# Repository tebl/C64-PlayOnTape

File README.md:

# C64 PlayOnTape
Remember waiting around for what sometimes would feel like forever, just to get your favourite game loaded from your trusty datasette? Well, now you can now attempt to return to a slightly less irritating version of those good old days - loading games'll take just as long as they did back then, just without the need to fiddle with the azimuth setting. Based on the rather excellent [tapuino](https://github.com/sweetlilmre/tapuino) project, there's even an accompanying [blog](http://sweetlilmre.blogspot.com/search/label/Tapuino) that included instructions on how to build one all by yourself.

Personally I haven't had much success building prototypes on breadboards, veroboard and almost every other option available within my severely limited cashflow. I highly suspect that part of this is due to my tendency for only buying the cheapest stuff around, so in order to keep myself sane I went straight from the blog onto designing the PCBs in KiCAD. On the plus side the files are here for anyone to enjoy, just remember that there's no warranty beyond my promise that it worked that one time I built one. If your C64 blows up due to problems assembling or using it, know that I'll be happy to take it off your hands for spare parts.

- [C64 PlayOnTape](#c64-playontape)
  - [1.1> Modules](#11-modules)
  - [1.2> Acknowledgements](#12-acknowledgements)

## 1.1> Modules
For the technical details as well as information regarding the modules included by this specific github project, consult the table below. Follow the documentation links for build instructions, BOM and anything else you'd for that specific module. Faceplates and any backplates listed are for the most most part only decorative, allowing you to put together something similar to a case without actually requiring a 3d-printer. Also, check out the [schematics](https://github.com/tebl/C64-PlayOnTape/tree/main/documentation/schematic) for more information about the electronic side of things.

| Module                 | Required    | Documentation                      | Order      |
| ---------------------- | ----------- | ---------------------------------- | ---------- |
| [C64 PlayOnTape Module](https://github.com/tebl/C64-PlayOnTape/tree/main/PlayOnTape%20Module) | Yes | [Documentation](https://github.com/tebl/C64-PlayOnTape/blob/main/PlayOnTape%20Module/README.md), [BOM](https://github.com/tebl/C64-PlayOnTape/blob/main/PlayOnTape%20Module/README.md#3-bom), [Getting started](https://github.com/tebl/C64-PlayOnTape/blob/main/documentation/getting_started.md) | [PCBWay](https://www.pcbway.com/project/shareproject/C64_PlayOnTape_7281e4c0.html)
| [C64 PlayOnTape Adapter](https://github.com/tebl/C64-PlayOnTape/tree/main/PlayOnTape%20Adapter) | Yes | [Documentation](https://github.com/tebl/C64-PlayOnTape/blob/main/PlayOnTape%20Adapter/README.md), [BOM](https://github.com/tebl/C64-PlayOnTape/blob/main/PlayOnTape%20Adapter/README.md#3-bom) | [PCBWay](https://www.pcbway.com/project/shareproject/C64_PlayOnTape_Adapter_6b7e3197.html)
| [PlayOnTape Backplate](https://github.com/tebl/C64-PlayOnTape/tree/main/faceplates/PlayOnTape%20Backplate) | No | [Documentation](https://github.com/tebl/C64-PlayOnTape/blob/main/faceplates/PlayOnTape%20Backplate/README.md) | [PCBWay](https://www.pcbway.com/project/shareproject/C64_PlayOnTape_Backplate_04d028fa.html)
| [PlayOnTape Faceplate (A1)](https://github.com/tebl/C64-PlayOnTape/tree/main/faceplates/PlayOnTape%20Faceplate%20A1) | Recommended | [Documentation](https://github.com/tebl/C64-PlayOnTape/blob/main/faceplates/PlayOnTape%20Faceplate%20A1/README.md), [BOM](https://github.com/tebl/C64-PlayOnTape/blob/main/faceplates/PlayOnTape%20Faceplate%20A1/README.md#3-bom) | [PCBWay](https://www.pcbway.com/project/shareproject/C64_PlayOnTape_Faceplate_FA1_dac67ded.html)

## 1.2> Acknowledgements
Everything comes from something, in particular when it comes to most of my electronics projects. I mainly build things I would like to own, often doing a respin to fit my own particular style and preferences with most of the hardest parts of the designs already provided by people more knowledgable than I. As already mentioned, my designs are based on the rather excellent [tapuino](https://github.com/sweetlilmre/tapuino) project with a new name just to keep things separate, for more details on how it functions - check out his accompanying [blog](http://sweetlilmre.blogspot.com/search/label/Tapuino) as well.

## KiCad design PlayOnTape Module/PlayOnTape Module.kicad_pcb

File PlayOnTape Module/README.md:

# PlayOnTape Module
Remember waiting around for what sometimes would feel like forever, just to get your favourite game loaded from your trusty datasette? Well, now you can now attempt to return to a slightly less irritating version of those good old days - loading games'll take just as long as they did back then, just without the need to fiddle with the azimuth setting. Based on the rather excellent [tapuino](https://github.com/sweetlilmre/tapuino) project, there's even an accompanying [blog](http://sweetlilmre.blogspot.com/search/label/Tapuino) that included instructions on how to build one all by yourself.

This is the main module, containing most if not all of the electronic circuit needed to make it all work as expected. By most, I mean that even though you can install the display directly on this module in order to build a minimal option, I would expect you to install the display on one of the [faceplates](https://github.com/tebl/C64-PlayOnTape/tree/main/faceplates). You will also need the [cable adapter](https://github.com/tebl/C64-PlayOnTape/tree/main/PlayOnTape%20Adapter) so that you have some way of connecting it to your Commodore 64, via a 6-pin IDC-cable.

- [PlayOnTape Module](#playontape-module)
  - [1> Building the module](#1-building-the-module)
    - [1.1> Installing the display](#11-installing-the-display) 
    - [1.2> Installing the firmware](#12-installing-the-firmware)
    - [1.3> Finishing steps](#13-finishing-steps)
  - [2> Schematic](#2-schematic)
  - [3> BOM](#3-bom)

# 1> Building the module
Start by checking out the [BOM](#3-bom) and verify that you have the components needed before continuing, it's beyond frustrating to realize you need just that single item before being able to complete the build - with shipping times from China being what they are, it's better to get it right the first time. Personally I find that if it's very cheap, I'll just order several different ones - just in case one gets delayed or lost somewhere.

Starting by doing a visual inspection of the PCB, familiarize yourself with the placement of components as ordered some time ago. This time, focusing in particular on determining on which side of the board that the components themselves should be soldered and their respective orientation.

As with all builds of this type we'll start by installing the smallest components first, usually going by the height of the components when sitting flush against the board. A good starting point will therefore be the three resistors, but because things are never all that easy - we'll need to pick a potentially more suitable value for R2 and R6. The reason for this is that the value needed would depend on the type of LEDs you are using, the common cheap coloured LEDs will work with this value as long as you resist the temptation to pick *blue* as any of the colours.

The more modern bright or even just clear LEDs have a significantly higher efficiency, meaning that they would likely burn out or simply remain uncomfortably bright at such a low resistor value! The textbook way of handling this kind of issue is reading the datasheet for your LEDs, noting down forward voltage drop and then calculating the proper value to use. Yeah, I'm not doing that either! Your other options are therefore to simply choose a safe value somewhere between 1k and 3k3 (depending on your preferences), try it out on a breadboard or hold off on this until the rest of the unit has been built up and can be powered. If you chose the latter, then you'd just carefully take aim and jam a resistor in there, hold it into place and see if it looks good to you.

Adding the single non-polarized capacitor is the next likely candidate, as a 100nF capacitor it would normally have the number *"104"* printed on it. I've also taken the time to install any sockets needed, mostly because they are cheap and it allows me to easily ~~steal~~ borrow the ICs for some later project - just make sure to line up the little indent marking the side with pin 1 so that it matches what is printed on the PCB itself.

Installing the *MicroSD Card Adapter* is easy as long as a few easy steps are followed, mostly just as shown in the images above. First we'll attach a bit of thick double-sided tape, often referenced to as mounting tape, to the top of the adapter MicroSD slot on the adapter. Just take care to leave enough room so that it does not cover up the little latches on the sides of the metal slot. When satisfied insert the pins into the holes, remove the backing on the tape and bend the module over so it ends up sitting flush against the board. Finish up by soldering the pins from the underside, then using trim the excess of the pins using a sturdy set of side-cutting pliers. Touch up the solder points afterwards, just to ensure that we didn't crack any of the joints when doing the cutting.

Continuing on with the build process, we've added the 6-pin male straight IDC-connector - ensuring that we get the keying in the correct place - followed by adding the switches need to control the device. The LEDs we've already mentioned earlier, but here we've finally gotten to the point of actually installing them - ensuring that the longer pin goes into the round hole.

The board also features a single electrolytic capacitor that we should probably find a place for, this component has a polarity that we need to pay attention to. The line on the component needs to be matched up with the filled in area on the footprint, this will also match up the longer leg with the side marked with a tiny *"+"*. While the circuit doesn't require a specific voltage rating, I recommend using a 16v component as the higher rated parts will be physically larger and taller (causing problems with fitting it under the faceplate). 

The Arduino Nano is attached to the board using standard male pin-headers, these need to be soldered in somewhat straight - or - you may encounter soldering in the Arduino itself. The pin headers on the far-right have also been added, these are used to connect the signals required by the faceplate. 

**NB!** If you have a relatively high expectation in regards to the quality of your components, then there is the option of constructing a device that is slightly thinner. The process is simply to install 8mm hex standoffs, trimming the tops of the Arduino pins, then soldering the longer variety of the pin headers for the right-most pins directly to the faceplate instead of making it detachable (you may need to use longer pin headers or a small section of ribbon cable). Understandably enough, you'd hold off on doing this until every other component has been fitted.

The Arduino is then inserted onto the pins, then soldered into place though experience should tell us that we should at least test the device before soldering it onto a board - an easy enough test is to simply check that we are able to compile and upload a *blink*-sketch to it beforehand. The remaining ICs are then inserted into the sockets, ensuring that the indent, or dot in the case of the 4N35, is matched up with the indent found on the sockets.

As you will no doubt intend to use this module with a faceplate, we'll need to add some M3x10mm nylon hex standoffs to the mounting holes on the far corners of the board. Add a set of M3 nylon hex nuts on the bottom as needed with F-M standoffs, M3 nylon screws when used with F-F hex standoffs instead. This is also a suitable time to take a detour, mainly by building your [faceplate](https://github.com/tebl/C64-PlayOnTape/tree/main/faceplates) of choice then jump to [1.2> Installing firmware](#12-installing-firmware) once that's been completed and installed.

## 1.1> Installing the display
Skip this section if you chose to install the display on a [faceplate](https://github.com/tebl/C64-PlayOnTape/tree/main/faceplates), instead choosing to build a slightly cheaper version of the device. Unfortunately there are several versions of the 128x64 I2C displays, some will have a different physical sizes though they'd look the same at the first glance. Two different displays are shown on the image below.

When used without a faceplate, both of these will work the same when installed onto the PCB-module - however, there is one **MAJOR DIFFERENCE** that we need to pay attentions to, and that is the fact that some versions of these displays will have their power pins swapped! We'll need to wire them up according to the display we have, this is done by linking JP1 and JP2 to account for this: looking at your display, if the first pin on your display is labelled as *GND* then you will need to link both of these across pins *1-2* (the little triangle denotes pin 1). If on the other hand, the first pin is labelled as *VCC* then we need to link pins *2-3*. 

Given the need for the display to clear the *MicroSD Card Adapter* already soldered to the board, I suggest soldering some female pin headers to the board and insert the display onto those pin headers. If you require some mechanical support to the display, you can install a M2 nylon hex standoff to the right side of the display (the mounting hole on the board will only align with the *original*-type of display shown earlier) 

## 1.2> Installing the firmware
Installing, or updating for that matter, the firmware is accomplished through the [Arduino IDE](https://www.arduino.cc/en/software). Start by downloading a copy of the sketch supplied by its original author, it's on [github](https://github.com/sweetlilmre/tapuino) and can simply click the green *Code*-button and then select *Download ZIP*. Extract somewhere that you'll be able to locate at a later point in time.

Within the directory of files you just extracted, remembering how I just seconds ago to you to put it somewhere that you'd be able to locate them again? All good? Cracking on then. Start by renaming the file called *config-user.h.example* to *config-user.h*, depending on your choice of operating system you may need to explicitly tell it to actually show you the extensions for the file. Why Microsoft constantly chooses to make things more difficult? I'll probably never know.

Editing the contents of the file we just renamed, now properly named *config-user.h*, we'll need to uncomment the lines specifying the type of display that we'll be using. Given that I've already forced you to use a 128x64 I2C OLED display, the lines relevant to us  are the following (in addition to specifying the language to use):
```
#define LCD_USE_SSD1306_OLED_MODULE
#define LCD_I2C_ADDR        0x3C // I2C address for the OLED
#define LCD_SSD1306_128x64

#define TAPUINO_LANGUAGE_EN
```

Opening up the Arduino sketch named *tapuino.ino* in the Arduino IDE, we'll need to start by configuring the type of Arduino we'll be using - specifying the *Arduino Nano* as your board.

With the board connected to your computer using a USB-cable, select the *port* provided by it (ideally you'll only have one option here, depending on whatever else you've got connected up to your system). At this point you should probably just attempt to verify and upload the sketch to your Arduino, in some cases the upload may end up looking like it got stuck until finally timing out a few minutes later. If that is the case, you may have the older version of the bootloader on your *Arduino Nano* and therefore you may need to select *ATmega328P (Old Bootloader)* from the *Processor* menu and try again.

If all goes well, your *C64 PlayOnTape* should initialize the display and potentially give you an error stating that it failed to initialize - this just means that an SD-card has not been inserted into the slot (remember that since we installed the upside down, we need to insert the card upside down as well). Detach the USB-cable and set it aside, we won't be needing that anymore.

**NB!** The *C64 PlayOnTape* should not be connected to your computer via the USB-cable when used with a Commodore 64. You might kill your Commodore 64, you might kill your laptop - so it is probably best not to.

## 1.3> Finishing steps
The last steps as should be expected is adding some screws on top to hold the faceplate firmly in place, connect it to the cable adapter using a 6-pin IDC cable and then connect it to you Commodore 64 with everything else powered off. With an SD-card inserted with some TAP-files ready to go, you can just select one and get to using it.

![Getting started](https://github.com/tebl/C64-PlayOnTape/raw/main/gallery/2022-05-22%2000.33.10.jpg
)

A simple guide on [getting started](https://github.com/tebl/C64-PlayOnTape/blob/main/documentation/getting_started.md) have been put together in order to cover this in slightly greater detail, check it out if you need a refresher on topics not already covered.

# 2> Schematic
The supplied KiCad files should be sufficient as both a schematic and as a  starting point for ordering PCBs (basically you could just zip the contents of the export folder and upload that on a fabrication site), the schematic is also available in [PDF-format](https://github.com/tebl/C64-PlayOnTape/tree/main/documentation/schematic) found within the schematics-part of the [documentation](https://github.com/tebl/C64-PlayOnTape/tree/main/documentation).

# 3> BOM
Most parts should be easy to get a hold of from your favourite local electronic component shop, but given that I don't have access to such shops where I live so everything was based on whatever I could get cheapest from eBay/AliExpress (free shipping, plan on waiting 3-4 weeks for delivery though). If you are in doubt what to order from a high-end electronics parts provider, I recommend that you study the pictures as the more common Chinese parts may be harder to find in the myriad of options presented there.

| Reference    | Item                                                 | Count | Order |
| ------------ | ---------------------------------------------------- | ----- | ----- |
| PCB          | Fabricate using Gerber files                         |     1 | [PCBWay](https://www.pcbway.com/project/shareproject/C64_PlayOnTape_7281e4c0.html)
| A1           | Arduino Nano (ATMega328)                             |     1 |
| A2           | MicroSD Card Adapter                                 |     1 |
| C1           | 220uF electrolytic capacitor (6.3mm x 2.5mm)         |     1 |
| C2           | 100nF ceramic capacitor (5mm)                        |     1 |
| D1,D2        | 5mm LEDs, preferably bright clear variety            |    (2)|
| IC1          | 128x64 I2C OLED display                              |    (1)|
| J1 *         | 2x3 pin straight male IDC-socket                     |     1 |
| J3           | 7-pin male straight pin header                       |     1 |
| J5           | 3-pin male straight pin header                       |     1 |
| R1           | 330 ohm resistor                                     |     1 |
| R2,R6 **     | 330 ohm resistor                                     |    (2)|
| SW1-SW4      | 6x6x5mm right-angle momentary button                 |     4 |
| U1           | 4N35 optocoupler (DIP-6)                             |     1 |
| U2           | CD4052 (DIP-16)                                      |     1 |
| Cable        | 6-pin IDC cable                                      |     1 |
| Mounting *** | Nylon M3 hex standoffs 10mm (M-F)                    |     4 |
| Mounting *** | Nylon M3 nylon nuts                                  |     4 |
| Mounting *** | Nylon M3x6mm nylon screws                            |     4 |

*) This could be replaced by standard male pin headers if you wanted to, but using the keyed IDC-connector is recommended in order to avoid accidents.
**) Resistor needs to have a value suitable for use with the type of LED installed. For modern bright LEDs consider using a value from 1k to 3k3 to avoid being completely blinded, better yet - check the datasheet and do the math.
***) These are used in various places of the project, these are available in the form of kits usually advertised *M3 nylon standoff kit* which should contain most of what you'd need.

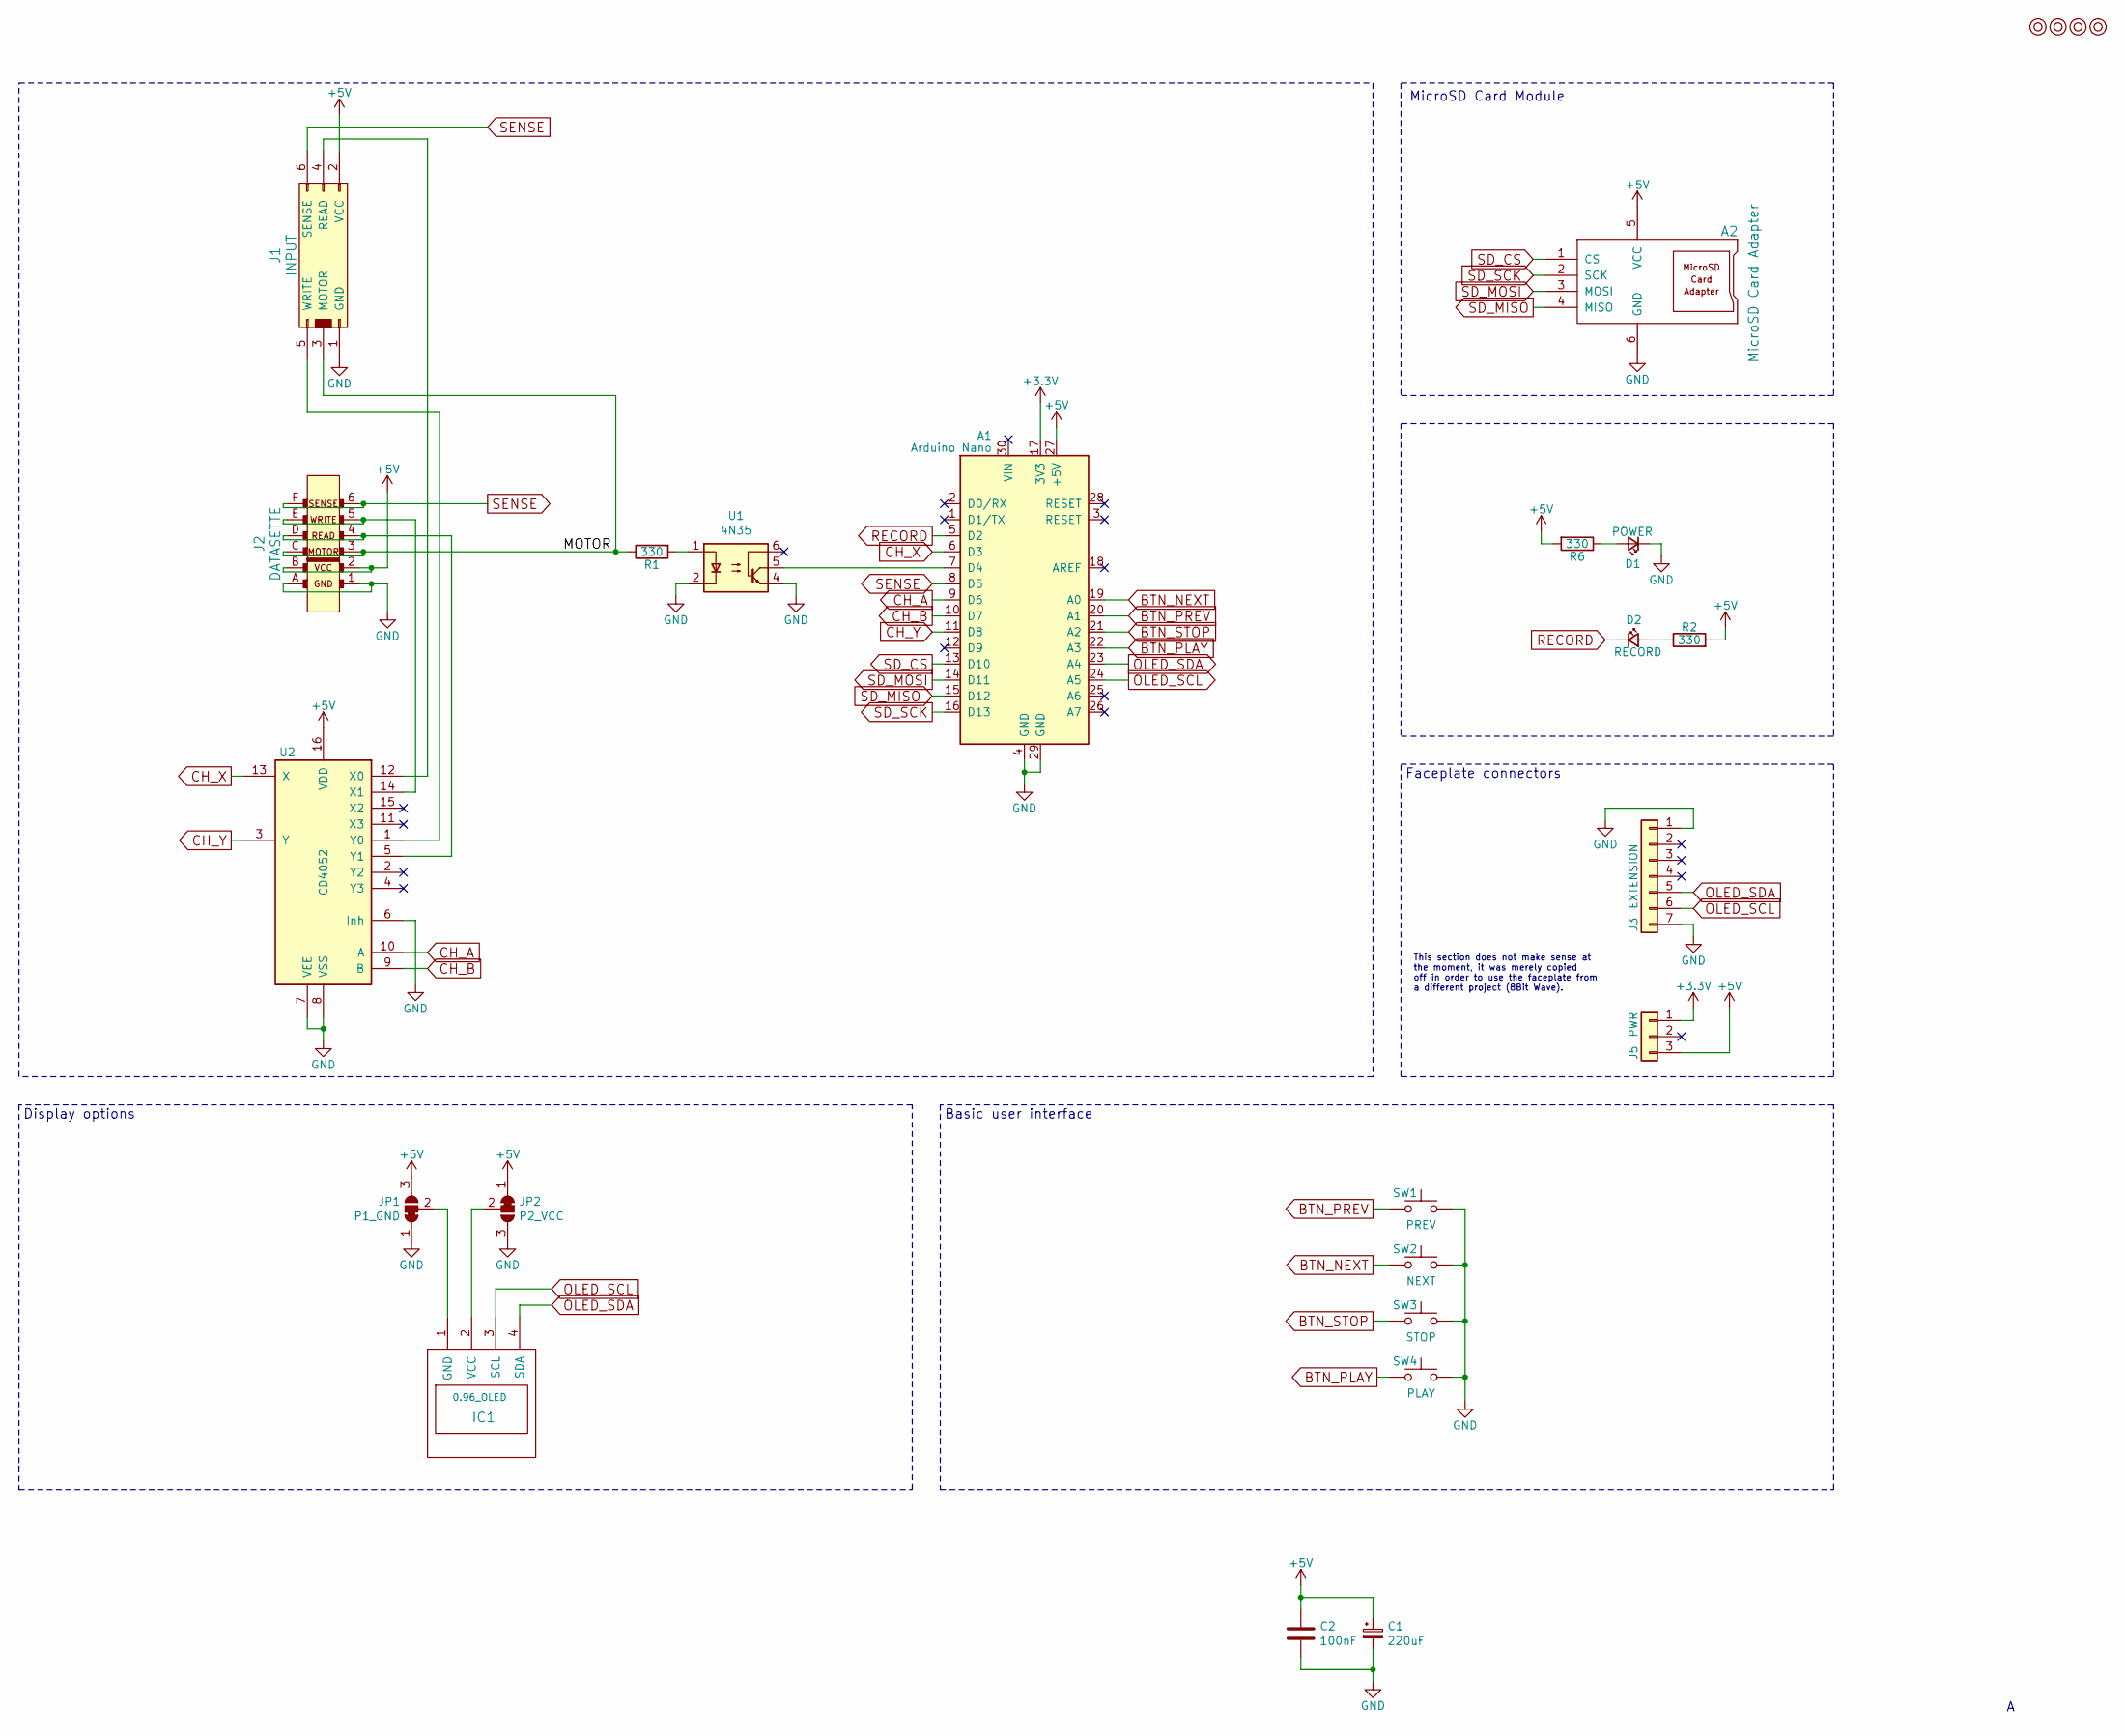
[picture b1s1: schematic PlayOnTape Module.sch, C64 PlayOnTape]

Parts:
A1: Arduino Nano; Arduino_Nano
A2: MicroSD Card Adapter; MicroSD_Card_Adapter
C1: 220uF; CP_Radial_D6.3mm_P2.50mm
C2: 100nF; C_Disc_D4.7mm_W2.5mm_P5.00mm
D1: POWER; LED_D5.0mm
D2: RECORD; LED_D5.0mm
IC1: 0.96_OLED; 0.96_I2C_OLED
J1: INPUT; IDC-Header_2x03_P2.54mm_Vertical
J2: DATASETTE; C64-Cassette-Port
J3: EXTENSION; Pin_Header_Straight_1x07_Pitch2.54mm
J5: PWR; PinHeader_1x03_P2.54mm_Vertical
JP1: P1_GND; SolderJumper-3_P1.3mm_Open_RoundedPad1.0x1.5mm
JP2: P2_VCC; SolderJumper-3_P1.3mm_Open_RoundedPad1.0x1.5mm
M1, M2, M3, M4: Mounting; M3
R1, R2, R6: 330; R_Axial_DIN0207_L6.3mm_D2.5mm_P10.16mm_Horizontal
SW1: PREV; SW_Tactile_SPST_Angled_PTS645Vx31-2LFS
SW2: NEXT; SW_Tactile_SPST_Angled_PTS645Vx31-2LFS
SW3: STOP; SW_Tactile_SPST_Angled_PTS645Vx31-2LFS
SW4: PLAY; SW_Tactile_SPST_Angled_PTS645Vx31-2LFS
U1: 4N35; DIP-6_W7.62mm_Socket_LongPads
U2: CD4052; DIP-16_W7.62mm_Socket_LongPads

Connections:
+3V3: A1.17 (3V3), J5.1
+5V: A1.27 (+5V), A2.5 (VCC), C1.1, C2.1, J1.2 (VCC), J2.2 (VCC), J2.B (VCC), J5.3, JP1.3 (B), JP2.1 (A), R2.2, R6.2, U2.16 (VDD)
/MOTOR: J1.3 (MOTOR), J2.3 (MOTOR), J2.C (MOTOR), R1.1
BTN_NEXT: A1.19 (A0), SW2.1
BTN_PLAY: A1.22 (A3), SW4.1
BTN_PREV: A1.20 (A1), SW1.1
BTN_STOP: A1.21 (A2), SW3.1
CH_A: A1.9 (D6), U2.10 (A)
CH_B: A1.10 (D7), U2.9 (B)
CH_X: A1.6 (D3), U2.13 (X)
CH_Y: A1.11 (D8), U2.3 (Y)
GND: A1.4 (GND), A1.29 (GND), A2.6 (GND), C1.2, C2.2, D1.1 (K), J1.1 (GND), J2.1 (GND), J2.A (GND), J3.1, J3.7, JP1.1 (A), JP2.3 (B), SW1.2, SW2.2, SW3.2, SW4.2, U1.2, U1.4, U2.6 (Inh), U2.7 (VEE), U2.8 (VSS)
unnamed: A1.7 (D4), U1.5
unnamed: D1.2 (A), R6.1
unnamed: D2.2 (A), R2.1
unnamed: IC1.1 (GND), JP1.2 (C)
unnamed: IC1.2 (VCC), JP2.2 (C)
unnamed: J1.4 (READ), U2.12 (X0)
unnamed: J1.5 (WRITE), U2.1 (Y0)
unnamed: J2.4 (READ), J2.D (EREAD), U2.5 (Y1)
unnamed: J2.5 (WRITE), J2.E (WRITE), U2.14 (X1)
unnamed: R1.2, U1.1
OLED_SCL: A1.24 (A5), IC1.3 (SCL), J3.6
OLED_SDA: A1.23 (A4), IC1.4 (SDA), J3.5
RECORD: A1.5 (D2), D2.1 (K)
SD_CS: A1.13 (D10), A2.1 (CS)
SD_MISO: A1.15 (D12), A2.4 (MISO)
SD_MOSI: A1.14 (D11), A2.3 (MOSI)
SD_SCK: A1.16 (D13), A2.2 (SCK)
SENSE: A1.8 (D5), J1.6 (SENSE), J2.6 (SENSE), J2.F (SENSE)

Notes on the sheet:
Faceplate connectors
This section does not make sense at the moment, it was merely copied off in order to use the faceplate from a different project (8Bit Wave).
Basic user interface
Display options
MicroSD Card Module

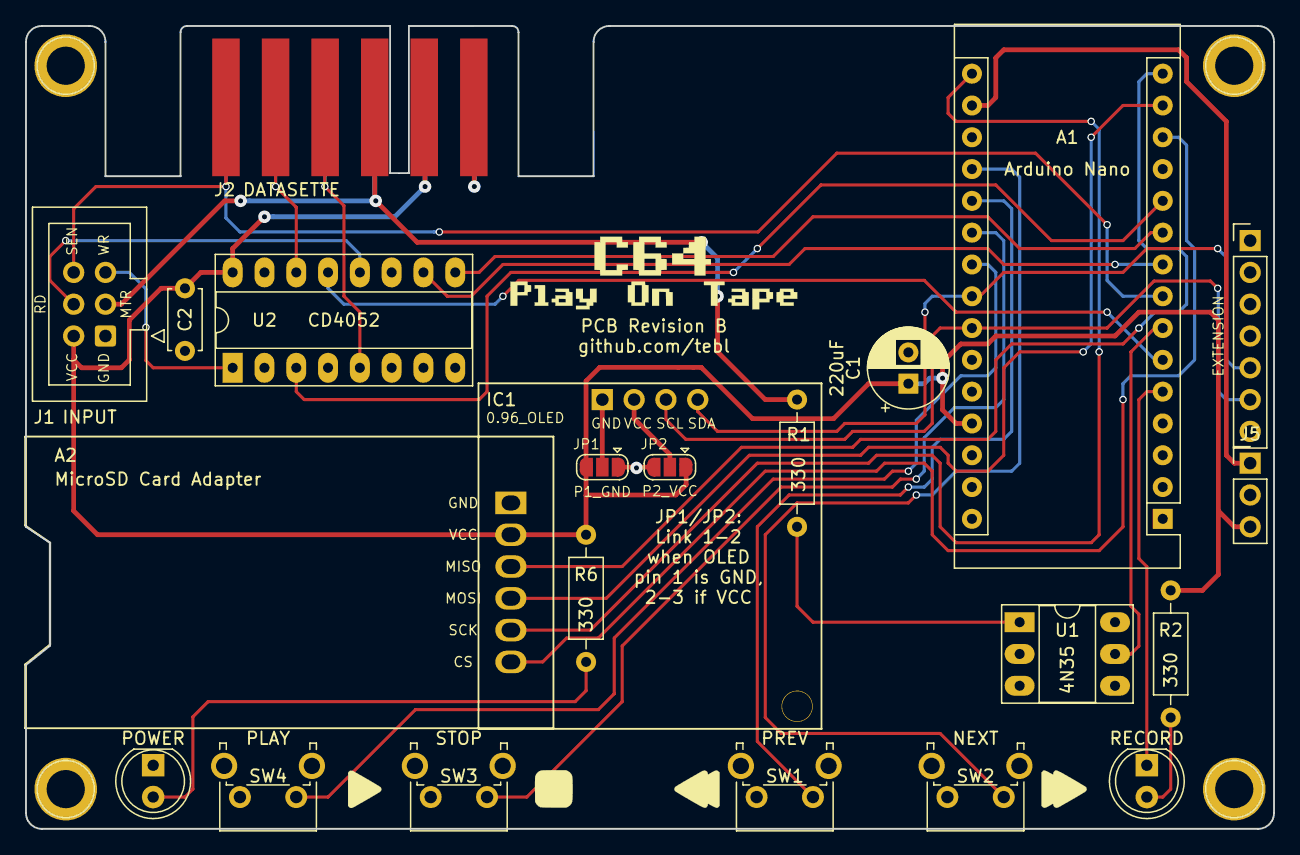
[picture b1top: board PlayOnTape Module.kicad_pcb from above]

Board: 2 copper layers, 99.7 x 64.1 mm, 26 parts (0 on the bottom side), 30 nets.

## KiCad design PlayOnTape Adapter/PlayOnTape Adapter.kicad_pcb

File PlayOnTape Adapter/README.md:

# PlayOnTape Adapter
Originally I designed the [C64 PlayOnTape](https://github.com/tebl/C64-PlayOnTape) with the idea that I would simply solder the cable straight to a connector and call it a day, but then I remembered that I've always loathed soldering cables thought that might be a case of having both too many and too few thumbs depending on the situation. The following revision was therefore redesigned with this little adapter board, so that the two can be connected using a commonly sold 2x3 pin IDC flat ribbon cable (usually sold as a *"6pin IDC JTAG ISP"*-cable on ebay and similar sites).

- [PlayOnTape Adapter](#playontape-adapter)
  - [1> Building the module](#1-building-the-module)
  - [2> Schematic](#2-schematic)
  - [3> BOM](#3-bom)

## 1> Building the module
Start by checking out the [BOM](#3-bom) and verify that you have the components needed before continuing, it's beyond frustrating to realize you need just that single item before being able to complete the build - with shipping times from China being what they are, it's better to get it right the first time. Personally I find that if it's very cheap, I'll just order several different ones - just in case one gets delayed or lost somewhere.

Starting by doing a visual inspection of the PCB, familiarize yourself with the placement of components as ordered - in particular, which side of the board that the components themselves should be soldered. Towards the sides there is a slot for holding a couple of M3-nuts, this is used to keep the connector from breaking away due to handling.

The 805-series connector comes in two variants, one with wider contacts that can have wires soldered to them and the more narrow pins intended for inserting into and soldering onto a PCB. We're - almost - not doing any of that, so either variant will be fine. Instead we will be soldering it an angle onto the side of the PCB as shown above, but since we want it to be a somewhat mechanically good connection we'll start by attaching it using the nylon M3-nuts and screws. The nuts'll only fit in the way that is shown, for the screws we'll just screw it through the connector and into the nut (cutting down the length of the screws as needed).

When the screws are fitted into place, it should hold the connector well enough that we can look into soldering it into place. At this point you'll usually have the pins hovering somewhat over the PCB, this is easily rectified by using the flat edge of a screwdriver to push each of them at angle so that they align with the pads below. Then, we just solder each of the pins into place, using plenty of solder to give it some added support.

The last part is just adding the 2x3 pin IDC male straight socket, ensuring that the keying ends up in the correct orientation. At the bottom between some of the 805-series connector pins there is also a white line, this should match the keying one would expect to be used with the Commodore 64s cassette port. I don't think there's anything sold that would work, but you can easily make it from a piece of plastic by following a video by [Hey Birt!](https://www.youtube.com/c/HeyBirt) on the topic of [stupid proofing your edge connectors](https://www.youtube.com/watch?v=vWt5WGZH8hI).

# 2> Schematic
The supplied KiCad files should be sufficient as both a schematic and as a  starting point for ordering PCBs (basically you could just zip the contents of the export folder and upload that on a fabrication site), the schematic is also available in [PDF-format](https://github.com/tebl/C64-PlayOnTape/tree/main/documentation/schematic) found within the schematics-part of the [documentation](https://github.com/tebl/C64-PlayOnTape/tree/main/documentation).

# 3> BOM
Most parts should be easy to get a hold of from your favourite local electronic component shop, but given that I don't have access to such shops where I live so everything was based on whatever I could get cheapest from eBay/AliExpress (free shipping, plan on waiting 3-4 weeks for delivery though). If you are in doubt what to order from a high-end electronics parts provider, I recommend that you study the pictures as the more common Chinese parts may be harder to find in the myriad of options presented there.

| Reference    | Item                                                 | Count | Order |
| ------------ | ---------------------------------------------------- | ----- | ----- |
| PCB          | Fabricate using Gerber files                         |     1 | [PCBWay](https://www.pcbway.com/project/shareproject/C64_PlayOnTape_Adapter_6b7e3197.html)
| J1 *         | 2x3 pin straight male IDC-socket                     |     1 |
| J2           | 12-pin 805-series 3.96mm card edge connector         |     1 |
| Cable        | 6-pin IDC cable                                      |     1 |

*) This could be replaced by standard male pin headers if you wanted to, but using the keyed IDC-connector is recommended in order to avoid accidents.

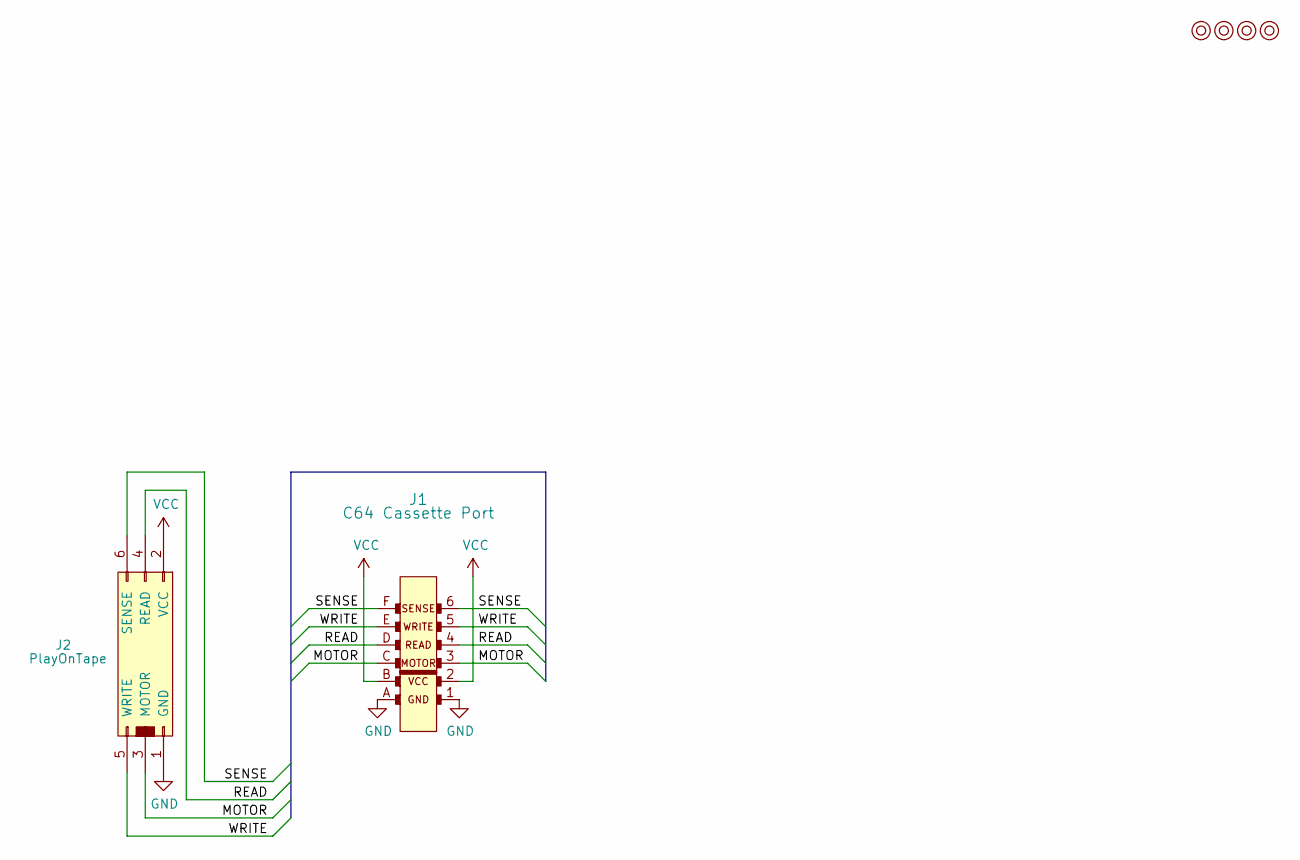
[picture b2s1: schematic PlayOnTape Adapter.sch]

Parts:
J1: C64 Cassette Port; C64_Cassette-Edge
J2: PlayOnTape; IDC-Header_2x03_P2.54mm_Vertical
M1, M2, M3, M4: Mounting; M3_pin

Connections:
/MOTOR: J1.3 (MOTOR), J1.C (MOTOR), J2.3 (MOTOR)
/READ: J1.4 (READ), J1.D (EREAD), J2.4 (READ)
/SENSE: J1.6 (SENSE), J1.F (SENSE), J2.6 (SENSE)
/WRITE: J1.5 (WRITE), J1.E (WRITE), J2.5 (WRITE)
GND: J1.1 (GND), J1.A (GND), J2.1 (GND)
VCC: J1.2 (VCC), J1.B (VCC), J2.2 (VCC)

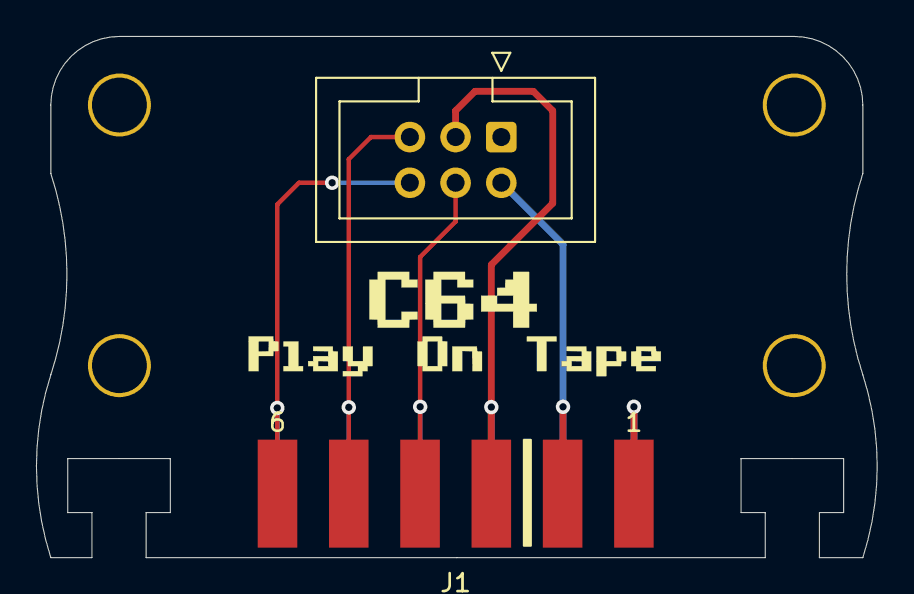
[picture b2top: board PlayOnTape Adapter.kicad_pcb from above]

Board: 2 copper layers, 46.7 x 29.0 mm, 6 parts (0 on the bottom side), 6 nets.

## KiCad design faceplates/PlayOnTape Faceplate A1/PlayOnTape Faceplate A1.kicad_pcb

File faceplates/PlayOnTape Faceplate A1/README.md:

# PlayOnTape Faceplate (A1)
The faceplate doesn't do all that much except making it look *"really really cool"*, to quote a *"really really cool"* comedy about male supermodels (Zoolander by the way, please don't judge my sense of humour)! To be perfectly honest you could actually do without the thing entirely, as the OLED-display could potentially be installed on the main module instead - however, what would the fun be in building a unit that'd be considerably less than what it was supposed to be? I'll leave that bit of decision-making up to you.

- [PlayOnTape Faceplate (A1)](#playontape-faceplate-a1)
  - [1> Building the module](#1-building-the-module)
  - [2> Schematic](#2-schematic)
  - [3> BOM](#3-bom)

## 1> Building the module
Start by checking out the [BOM](#3-bom) and verify that you have the components needed before continuing, it's beyond frustrating to realize you need just that single item before being able to complete the build - with shipping times from China as they are, better to get it right the first time (if it's very cheap I tend to order several just in case one gets delayed somewhere).

Before soldering anything together, you need to first determine which variation of the 128x64 SSD1306 OLED-display (0.96") you actually have - there is the **original** as designed for by this faceplate and there is the **new** version. The difference between the two is best spotted by looking at that the ribbon cable at the bottom display, the newer models models have a more narrow ribbon here as well as physical differences that's not as easy to spot from a picture on a listing. The two are functionally identical, but you need the original model as it is the version that fits properly with this specific faceplate.

The actual display usually comes with pin headers already installed, which is unfortunate as they are on the wrong side - refer to the pictures below to see how it is meant to fit into the mounting. You could always try desoldering the pins, but I've found that this is a rather cumbersome step - even with a desoldering station. The easiest solution however, is to melt the solder on a single pin using your soldering iron, then pushing the pin through the PCB using something metal like a pair of pliers. Please remember: heated metal burns, quite a bit to be honest!

If you've used the method of just pushing the pins through, then you should have a result as shown above - this is then almost ready for soldering into place, but we won't do that just yet. There are some things you must know before that.

If you went the route of desoldering the pin headers then just go ahead and add some new ones to the bottom of the faceplate and solder from the front of the board. The final step then is to find the pair of pliers you've already narrowly avoided using, to pull off the plastic bit from the pins we just soldered in. The result you're left with should look something like what is shown above.

The way forward from here should be fairly straight-forward, but as hinted at earlier there is one important details that we need to deal with first. Simply put, there are even more variations of these displays floating around, but worse yet - the VCC and GND pins have been swapped around (effectively killing the display if we're not lucky enough to catch it in time). The way we handle it here is that, on the back of the faceplate there are two sets of solder jumpers that need to be made - JP1 and JP2. These need to be shorted according to the order of pins used on the OLED-display, solder accross *1-2* if the first one is marked **GND**. Pins *2-3* if it is marked **VCC**. With the display shown above, I needed to solder both across pins *2-3* (the little triangle denotes pin 1).

To solder it into place, just put the screen face down so that it is visible through the window in the PCB and solder it into place. Use M2 nylon screws and nuts to affix the bottom, this keeps people from accidentally pushing the display into the case though you need to be careful not to overtighten these - doing so will easily crack the glass. 

As the last step, solder into place the female pin headers on the underside of the faceplate, preferably with the faceplate installed on the main module with the required standoffs between the two - this ensures a good mechanical connection between the them. Theoretically you could install extra long pin headers here and solder it directly to the module under, but that is only recommended when building several units at once and components being used have been verified as being of good quality.

# 2> Schematic
The supplied KiCad files should be sufficient as both a schematic and as a  starting point for ordering PCBs (basically you could just zip the contents of the export folder and upload that on a fabrication site), the schematic is also available in [PDF-format](https://github.com/tebl/C64-PlayOnTape/tree/main/documentation/schematic) found within the schematics-part of the [documentation](https://github.com/tebl/C64-PlayOnTape/tree/main/documentation).

# 3> BOM
Most parts should be easy to get a hold of from your favourite local electronic component shop, but given that I don't have access to such shops where I live so everything was based on whatever I could get cheapest from eBay/AliExpress (free shipping, plan on waiting 3-4 weeks for delivery though).

| Reference    | Item                                                 | Count |
| ------------ | ---------------------------------------------------- | ----- |
| PCB          | Fabricate using Gerber files                         |    (1)|
| IC1          | SSD1306 I2C OLED 128x64 (0.96") (**"original"**)     |    (1)|
| J1 *         | Female 3 pin header                                  |     1 |
| J3 *         | Female 7 pin header                                  |     1 |

*) J1 and J3 are placed right next to eachother, so you could just install a female 10 pin header here. That'll also reduce number of parts needed by one, if that matters.

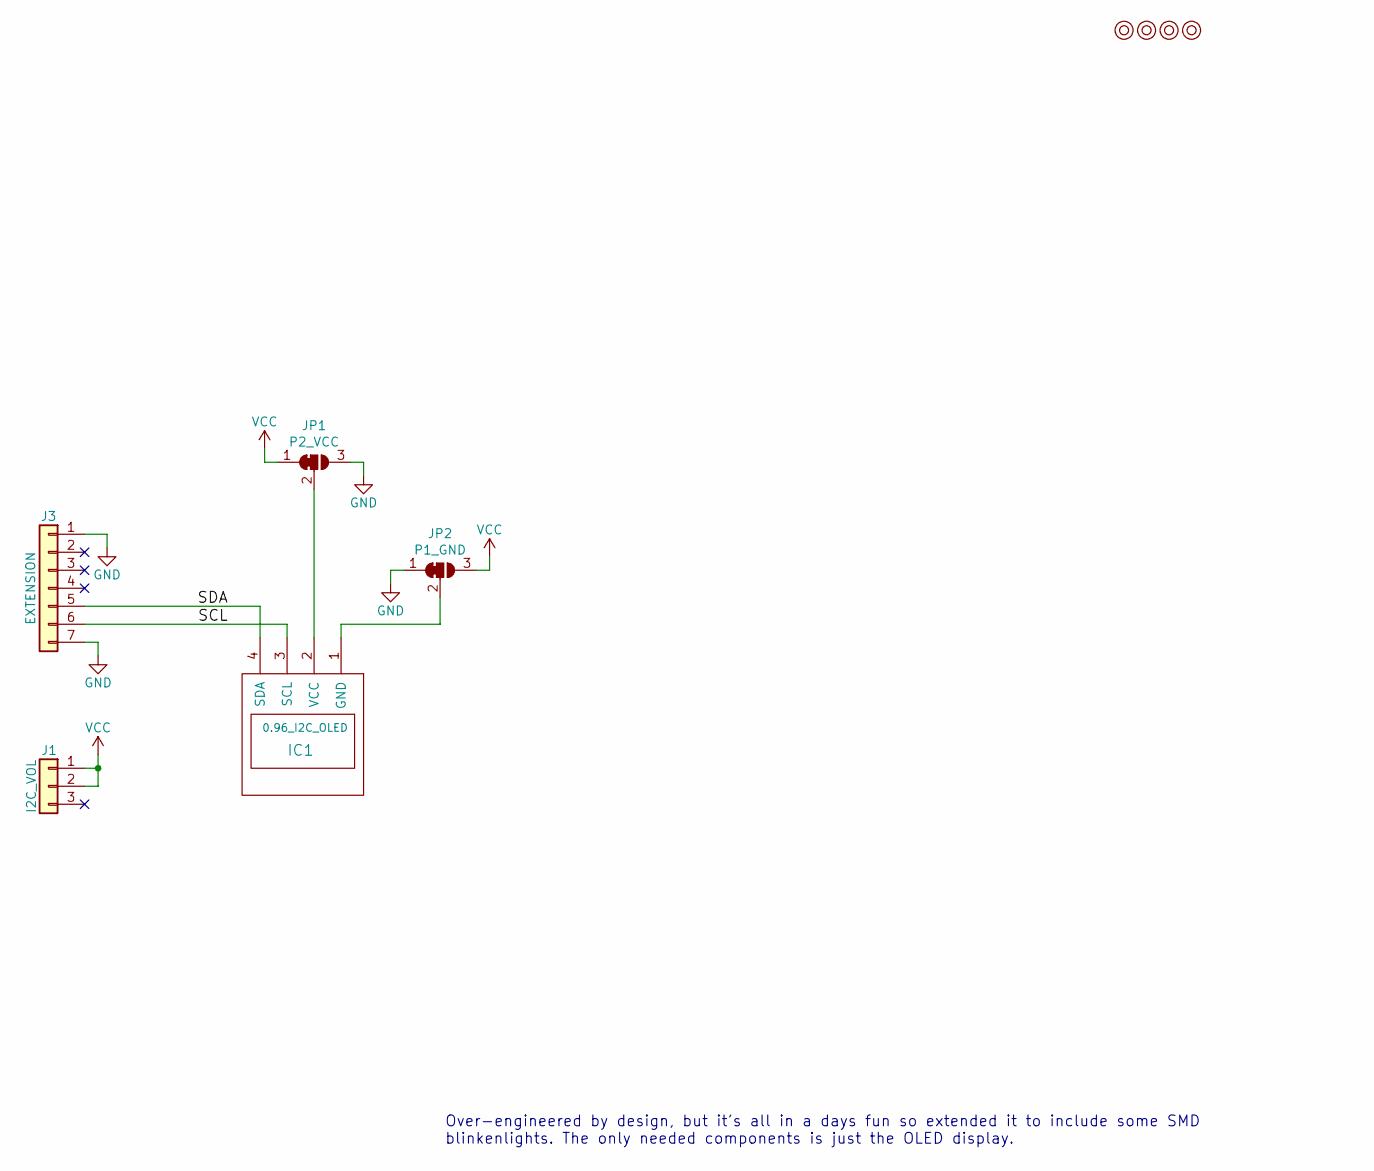
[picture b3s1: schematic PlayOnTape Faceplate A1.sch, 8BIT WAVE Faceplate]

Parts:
IC1: 0.96_I2C_OLED; 0.96_I2C_OLED2
J1: I2C_VOL; Pin_Header_Straight_1x03_Pitch2.54mm
J3: EXTENSION; Pin_Header_Straight_1x07_Pitch2.54mm
JP1: P2_VCC; SolderJumper-3_P1.3mm_Open_Pad1.0x1.5mm
JP2: P1_GND; SolderJumper-3_P1.3mm_Open_Pad1.0x1.5mm
M1, M2, M3, M4: Mounting; M3

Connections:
/SCL: IC1.3 (SCL), J3.6
/SDA: IC1.4 (SDA), J3.5
GND: J3.1, J3.7, JP1.3 (B), JP2.1 (A)
unnamed: IC1.1 (GND), JP2.2 (C)
unnamed: IC1.2 (VCC), JP1.2 (C)
VCC: J1.1, J1.2, JP1.1 (A), JP2.3 (B)

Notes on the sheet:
Over-engineered by design, but it's all in a days fun so extended it to include some SMD blinkenlights. The only needed components is just the OLED display.

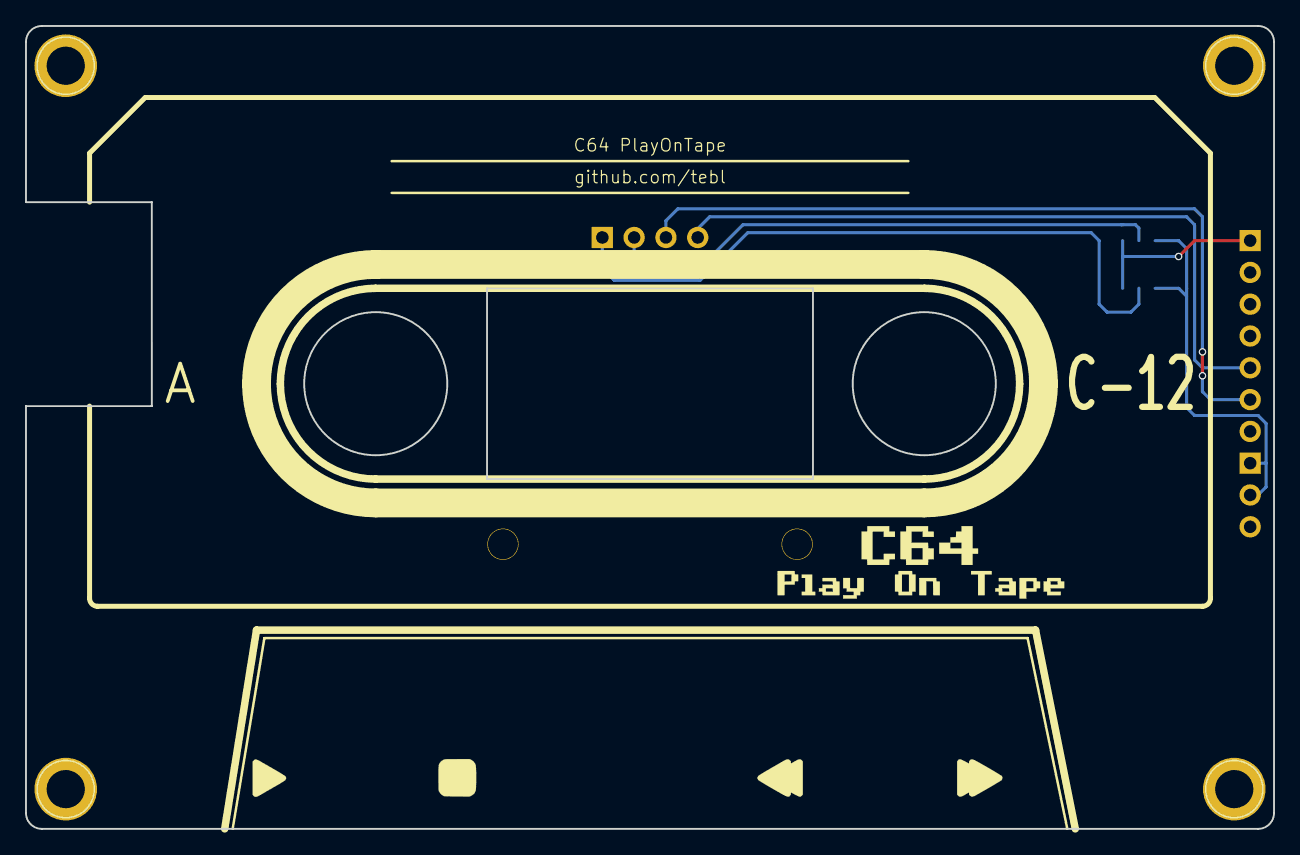
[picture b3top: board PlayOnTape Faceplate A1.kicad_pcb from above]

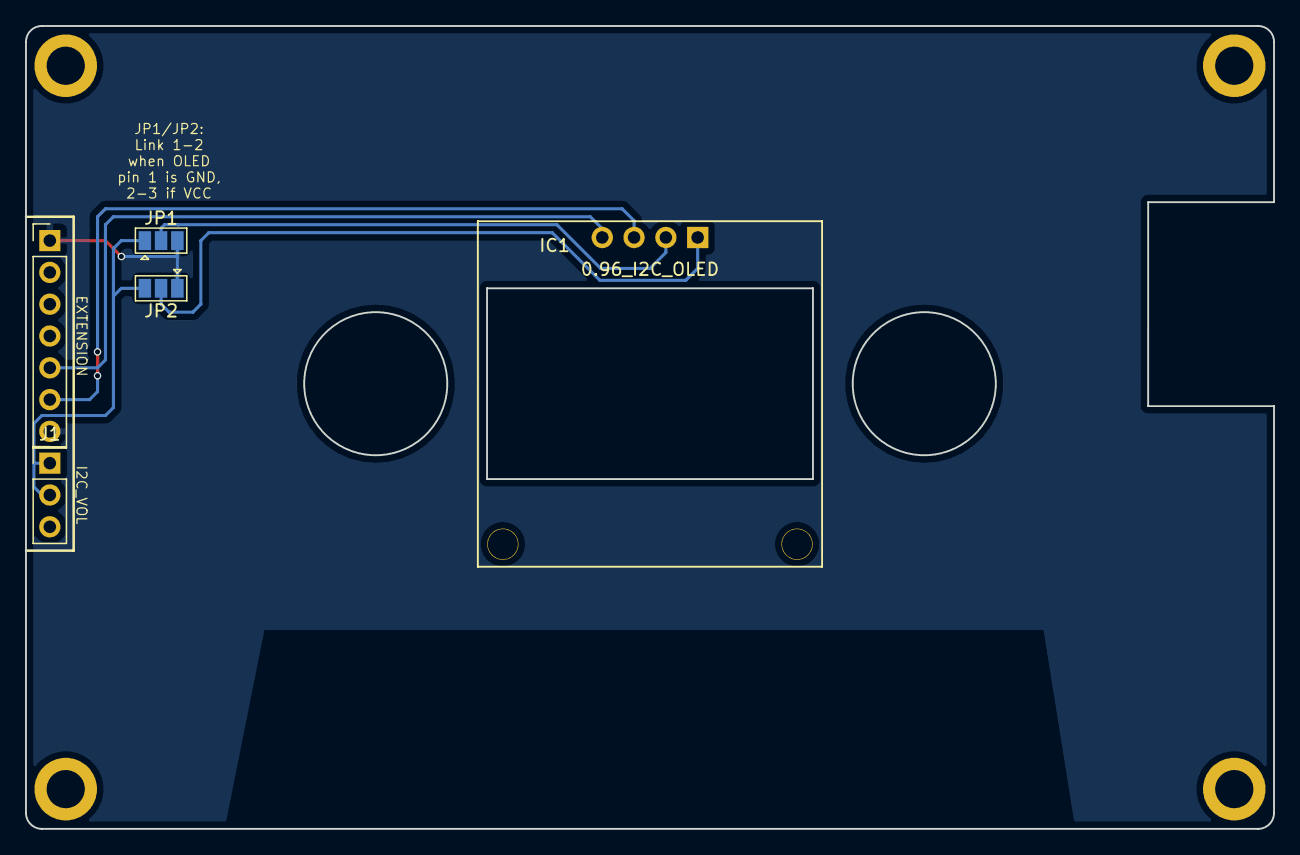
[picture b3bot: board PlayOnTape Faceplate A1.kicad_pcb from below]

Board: 2 copper layers, 99.7 x 64.1 mm, 9 parts (4 on the bottom side), 6 nets.

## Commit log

2022-01-28 From simple beginnings, a tape stops spinning - forevermore.
2022-01-29 Rough component placement
2022-01-29 Gerber export
2022-01-29 Beginning of README
2022-02-19 Move C1
2022-02-19 Enlarge SD adapter holes
2022-02-20 Add backplate
2022-02-20 Faceplate A1 added
2022-02-20 Tweak input mounting holes
2022-02-20 Reroute some tracks
2022-04-22 Build images
2022-04-22 Fixed OLED jumpers
2022-04-23 Changed to use IDC cable
2022-04-23 Remove old temporary files
2022-04-23 Add schematic
2022-04-23 Update schematic
2022-04-23 Remove temporary files
2022-04-23 Add connector cutout
2022-05-22 Silkscreen tweaks
2022-06-09 Fix link
2022-06-10 Tweak images
2022-06-10 Faceplate README
2022-06-10 Remove old image
2022-06-10 Added Adapter README
2022-06-11 Some build instructions added
2022-06-12 Added BOM
2022-06-12 Moved images

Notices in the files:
PlayOnTape Adapter/PlayOnTape Adapter.kicad_pcb:
Licensed under CERN OHL v1.2
